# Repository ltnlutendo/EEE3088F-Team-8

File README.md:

# EEE3088F-Team-8
Team collaboration for the EEE3088F 2022, HAT project

The HAT will serve primarily as a covid compliancy monitor for enclosed public venues like
lecture theatres, classrooms and supermarkets. The Hat will be connected to a STM32
discovery board which will handle computations and other processing. It will make use of
ultrasonic sensors that will be mounted on the venue entrance to capture the number of people
entering the venue. It will also incorporate pressure and temperature sensors to specifically
monitor room ventilation and determine whether the room is safe enough for its occupants.
Besides, covid related uses, the HAT could be used to compile statistical records on lecture
attendance or supermarket peak times. Furthermore, it can be used to monitor overcrowding on
shuttles like the Jammie buses in accordance with traffic and road safety regulations.

This is an ongoing project which is constantly improved 

## What you will need:
### Hardware
```
The HAT
A 3.7 Lithium ion rechargeble battery
A USB B to USB B micro cable
A laptop (Windows/MacOS/Linux)
5V power supply
STM32 Microcontroller
```
### Software
```
Atollic Studios
```

## Setting up software

Download the Atollic Studios from [this](https://www.st.com/en/development-tools/truestudio.html#:~:text=Featured%20Videos-,Description,easy%20and%20efficient%20development%20process.)

## Connecting the HAT

### Step 1: Powering up
```
Connect the HAT to the STM32, Make sure the usb port of the micro and the microcontroller are lined up 
- if the pins are mismatched, this can lead to a short circuit
The Green LED should be on when Plug is detected
```
### Step 2: Connecting to your laptop
```
Connect the USB cable to your laptop
Then connect the micro USB B to the HAT while holding the reset button(Blue button) of the micro controller.
```
### Step 3: Programming the HAT

Open Up your Atollic Studios, fork code from this [respiratory](https://github.com/ltnlutendo/EEE3088F-Team-8)
Paste this on the terminal and Run it to the micro controller.
Set the maximum variable to Max = 3 (This will set the maximum number of people allowed to enter to 3).
The blue LED will flash twice once the code is succesfully copied to the HAT's memory.

### Step 4: Getting ready to test

```
Put the hat flat on the table such that the sensors are not obstructed (1m unobstructed minimum distance).
```
### Step 5: Test

```
Wave your hand on top of the HAT 3 times, The buzzer should beep indicating maximum number of people entered.
```
### Well Done! You're all set up.

### Project Credits
- Power Submodule  - [Lutendo Mulaisi](https://github.com/ltnlutendo) 
- Sensor Submodule   - [Munashe Chihota](https://github.com/MunasheC)
- Interfacing Submodule - [Lisakhanya Miyani](https://github.com/LisakhanyaMiyana)
## How to contribute
You can contribute to this project using these [guidelines](https://www.contributor-covenant.org/)

## License
MIT License

Copyright (c) 2022 Team 8

Permission is hereby granted, free of charge, to any person obtaining a copy
of this software and associated documentation files (the "Software"), to deal
in the Software without restriction, including without limitation the rights
to use, copy, modify, merge, publish, distribute, sublicense, and/or sell
copies of the Software, and to permit persons to whom the Software is
furnished to do so, subject to the following conditions:

The above copyright notice and this permission notice shall be included in all
copies or substantial portions of the Software.

THE SOFTWARE IS PROVIDED "AS IS", WITHOUT WARRANTY OF ANY KIND, EXPRESS OR
IMPLIED, INCLUDING BUT NOT LIMITED TO THE WARRANTIES OF MERCHANTABILITY,
FITNESS FOR A PARTICULAR PURPOSE AND NONINFRINGEMENT. IN NO EVENT SHALL THE
AUTHORS OR COPYRIGHT HOLDERS BE LIABLE FOR ANY CLAIM, DAMAGES OR OTHER
LIABILITY, WHETHER IN AN ACTION OF CONTRACT, TORT OR OTHERWISE, ARISING FROM,
OUT OF OR IN CONNECTION WITH THE SOFTWARE OR THE USE OR OTHER DEALINGS IN THE
SOFTWARE.

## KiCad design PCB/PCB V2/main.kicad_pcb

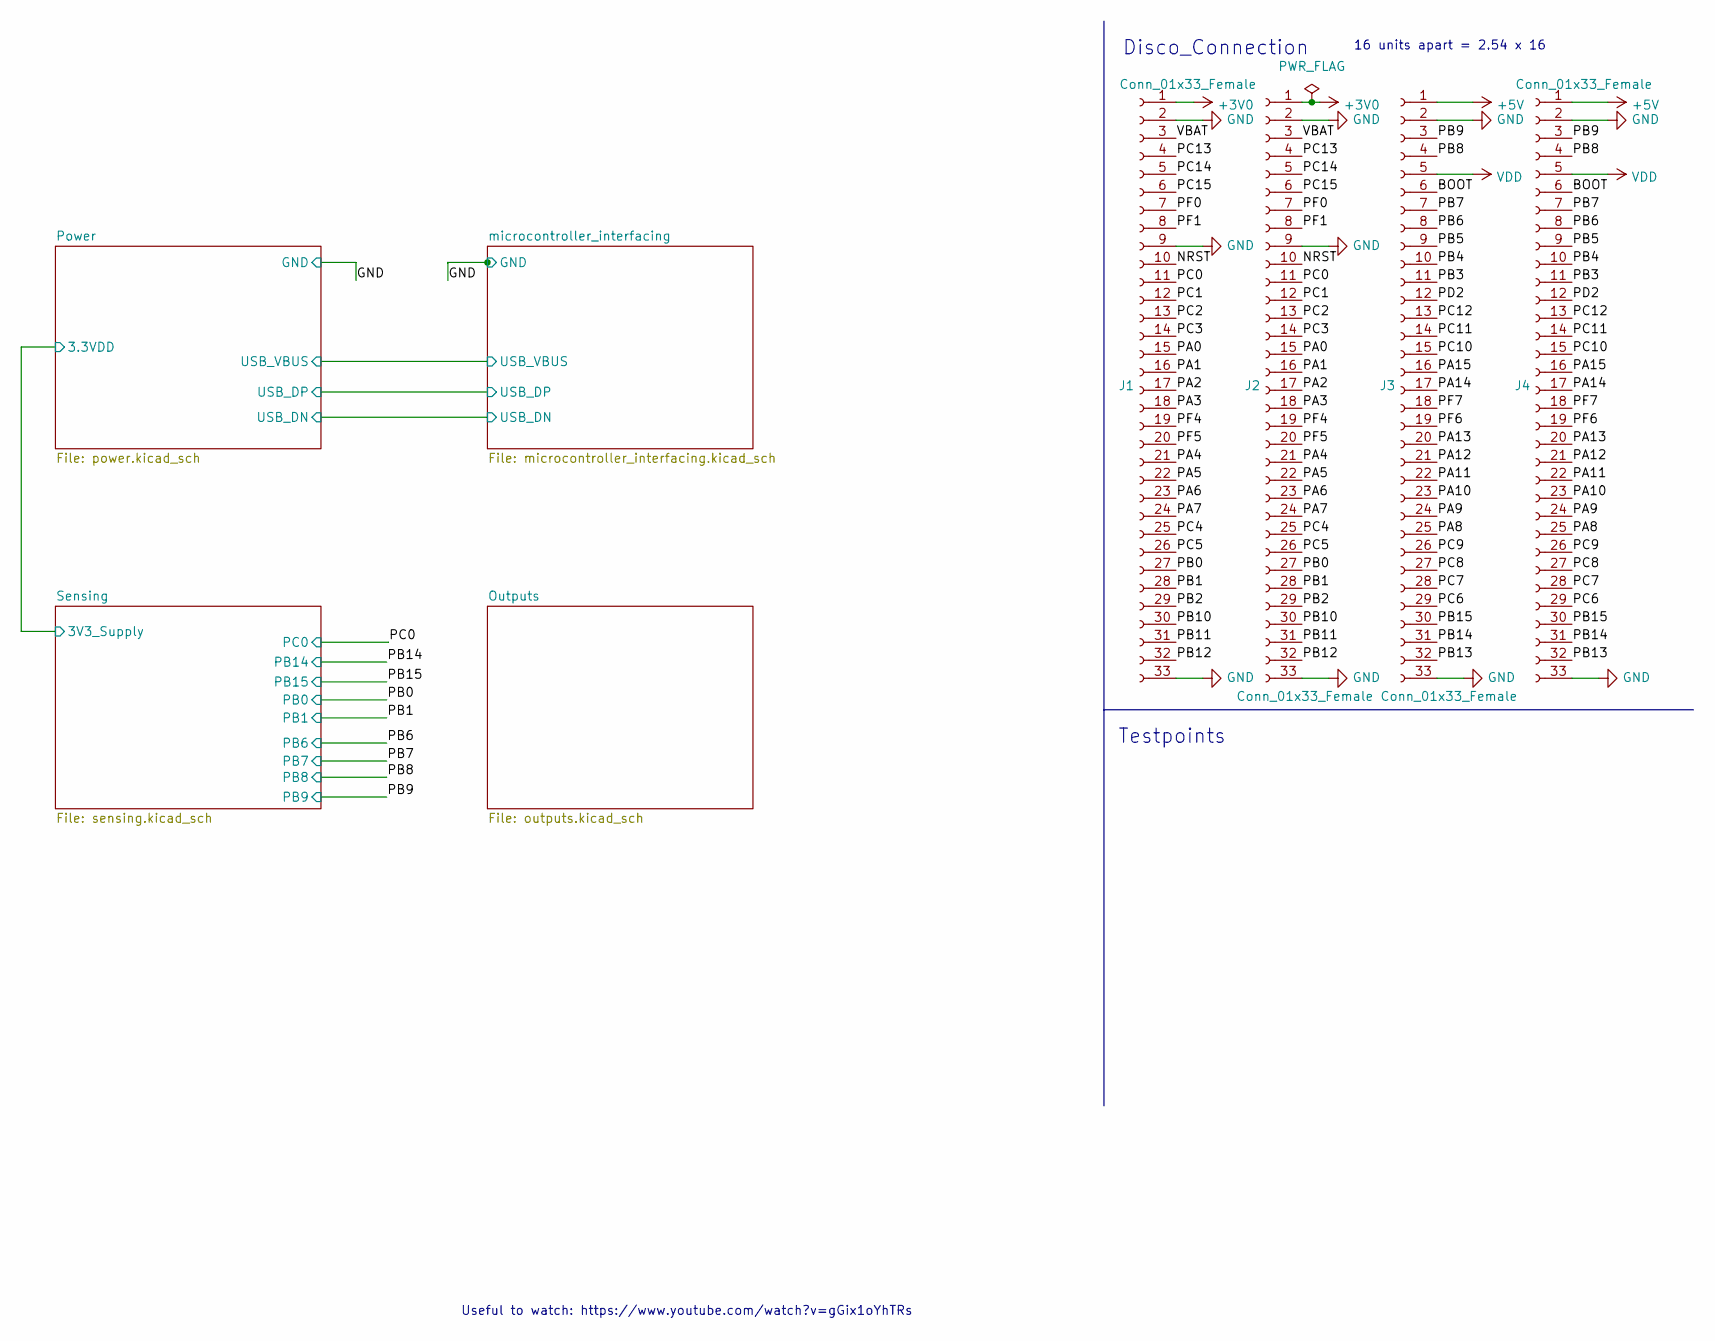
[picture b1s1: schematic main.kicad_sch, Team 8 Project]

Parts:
J1, J4: Conn_01x33_Female; PinHeader_1x33_P2.54mm_Vertical
J2, J3: Conn_01x33_Female; PinSocket_1x33_P2.54mm_Vertical; LCSC C1234 (example)

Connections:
+3V0: J1.1, J2.1
+3V3: J3.5, J4.5; also elsewhere on the board
/BOOT: J3.6, J4.6
/NRST: J1.10, J2.10
/PA0: J1.15, J2.15
/PA1: J1.16, J2.16
/PA2: J1.17, J2.17
/PA3: J1.18, J2.18
/PA4: J1.21, J2.21
/PA5: J1.22, J2.22
/PA6: J1.23, J2.23
/PA7: J1.24, J2.24
/PA8: J3.25, J4.25
/PA9: J3.24, J4.24
/PA10: J3.23, J4.23
/PA11: J3.22, J4.22
/PA12: J3.21, J4.21
/PA13: J3.20, J4.20
/PA14: J3.17, J4.17
/PA15: J3.16, J4.16
/PB0: J1.27, J2.27; also elsewhere on the board
/PB1: J1.28, J2.28; also elsewhere on the board
/PB2: J1.29, J2.29
/PB3: J3.11, J4.11
/PB4: J3.10, J4.10
/PB5: J3.9, J4.9
/PB6: J3.8, J4.8; also elsewhere on the board
/PB7: J3.7, J4.7; also elsewhere on the board
/PB8: J3.4, J4.4; also elsewhere on the board
/PB9: J3.3, J4.3; also elsewhere on the board
/PB10: J1.30, J2.30
/PB11: J1.31, J2.31
/PB12: J1.32, J2.32
/PB13: J3.32, J4.32
/PB14: J3.31, J4.31; also elsewhere on the board
/PB15: J3.30, J4.30; also elsewhere on the board
/PC0: J1.11, J2.11; also elsewhere on the board
/PC1: J1.12, J2.12
/PC2: J1.13, J2.13
/PC3: J1.14, J2.14
/PC4: J1.25, J2.25
/PC5: J1.26, J2.26
/PC6: J3.29, J4.29
/PC7: J3.28, J4.28
/PC8: J3.27, J4.27
/PC9: J3.26, J4.26
/PC10: J3.15, J4.15
/PC11: J3.14, J4.14
/PC12: J3.13, J4.13
/PC13: J1.4, J2.4
/PC14: J1.5, J2.5
/PC15: J1.6, J2.6
/PD2: J3.12, J4.12
/PF0: J1.7, J2.7
/PF1: J1.8, J2.8
/PF4: J1.19, J2.19
/PF5: J1.20, J2.20
/PF6: J3.19, J4.19
/PF7: J3.18, J4.18
/VBAT: J1.3, J2.3
GND: J1.2, J1.9, J1.33, J2.2, J2.9, J2.33, J3.2, J3.33, J4.2, J4.33; also elsewhere on the board

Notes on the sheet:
Useful to watch: https://www.youtube.com/watch?v=gGix1oYhTRs
16 units apart = 2.54 x 16
Disco_Connection
Testpoints

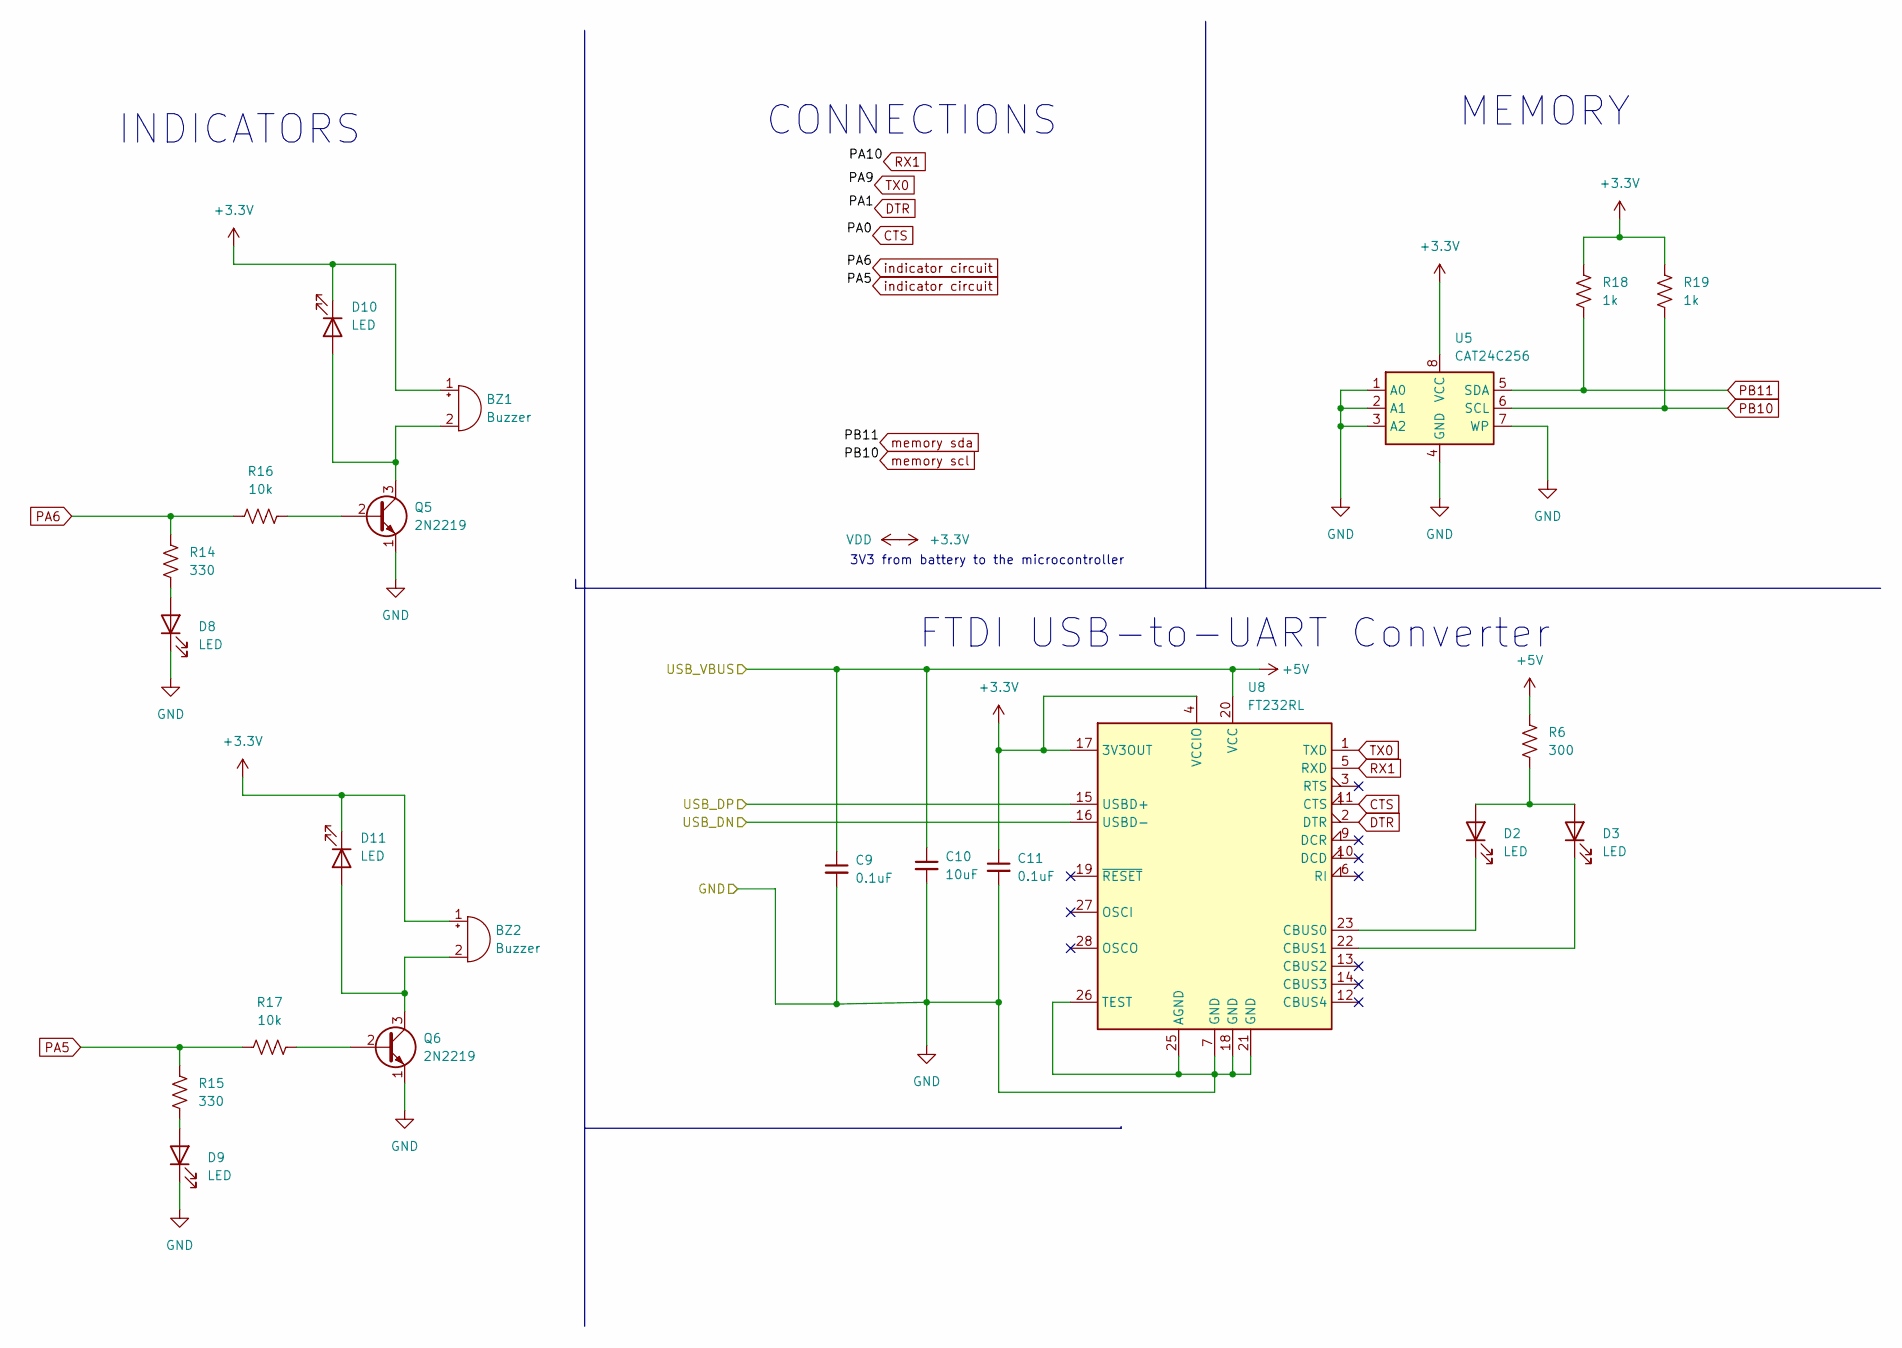
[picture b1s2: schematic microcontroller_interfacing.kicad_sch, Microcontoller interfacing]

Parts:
BZ1, BZ2: Buzzer; Buzzer_Murata_PKLCS1212E
C9, C11: 0.1uF; C_0805_2012Metric_Pad1.18x1.45mm_HandSolder
C10: 10uF; C_0805_2012Metric_Pad1.18x1.45mm_HandSolder
D2, D3, D8, D9, D10, D11: LED; LED_0805_2012Metric_Pad1.15x1.40mm_HandSolder
Q5, Q6: 2N2219; TO-39-3
R6: 300; R_0805_2012Metric_Pad1.20x1.40mm_HandSolder
R14, R15: 330; R_0805_2012Metric_Pad1.20x1.40mm_HandSolder
R16, R17: 10k; R_0805_2012Metric_Pad1.20x1.40mm_HandSolder
R18: 1k; R_0805_2012Metric_Pad1.20x1.40mm_HandSolder
R19: 1k; R_0805_2012Metric
U5: CAT24C256; SOIC-8_3.9x4.9mm_P1.27mm
U8: FT232RL; SSOP-28_5.3x10.2mm_P0.65mm

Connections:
+3V3: BZ1.1 (-), BZ2.1 (-), C11.1, D10.1 (K), D11.1 (K), R18.2, R19.2, U5.8 (VCC), U8.4 (VCCIO), U8.17 (3V3OUT); also elsewhere on the board
/Power/USB_DN: U8.16 (USBD-); also elsewhere on the board
/Power/USB_DP: U8.15 (USBD+); also elsewhere on the board
CTS: U8.11 (CTS)
DTR: U8.2 (DTR)
GND: C9.2, C10.2, C11.2, D8.1 (K), D9.1 (K), Q5.1 (E), Q6.1 (E), U5.1 (A0), U5.2 (A1), U5.3 (A2), U5.4 (GND), U5.7 (WP), U8.7 (GND), U8.18 (GND), U8.21 (GND), U8.25 (AGND), U8.26 (TEST); also elsewhere on the board
unnamed: BZ1.2 (+), D10.2 (A), Q5.3 (C)
unnamed: BZ2.2 (+), D11.2 (A), Q6.3 (C)
unnamed: D2.1 (K), U8.23 (CBUS0)
unnamed: D2.2 (A), D3.2 (A), R6.2
unnamed: D3.1 (K), U8.22 (CBUS1)
unnamed: D8.2 (A), R14.1
unnamed: D9.2 (A), R15.1
unnamed: Q5.2 (B), R16.2
unnamed: Q6.2 (B), R17.2
PB10: R19.1, U5.6 (SCL)
PB11: R18.1, U5.5 (SDA)
RX1: U8.5 (RXD)
TX0: U8.1 (TXD)

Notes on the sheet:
CONNECTIONS
MEMORY
FTDI USB-to-UART Converter
3V3 from battery to the microcontroller
INDICATORS

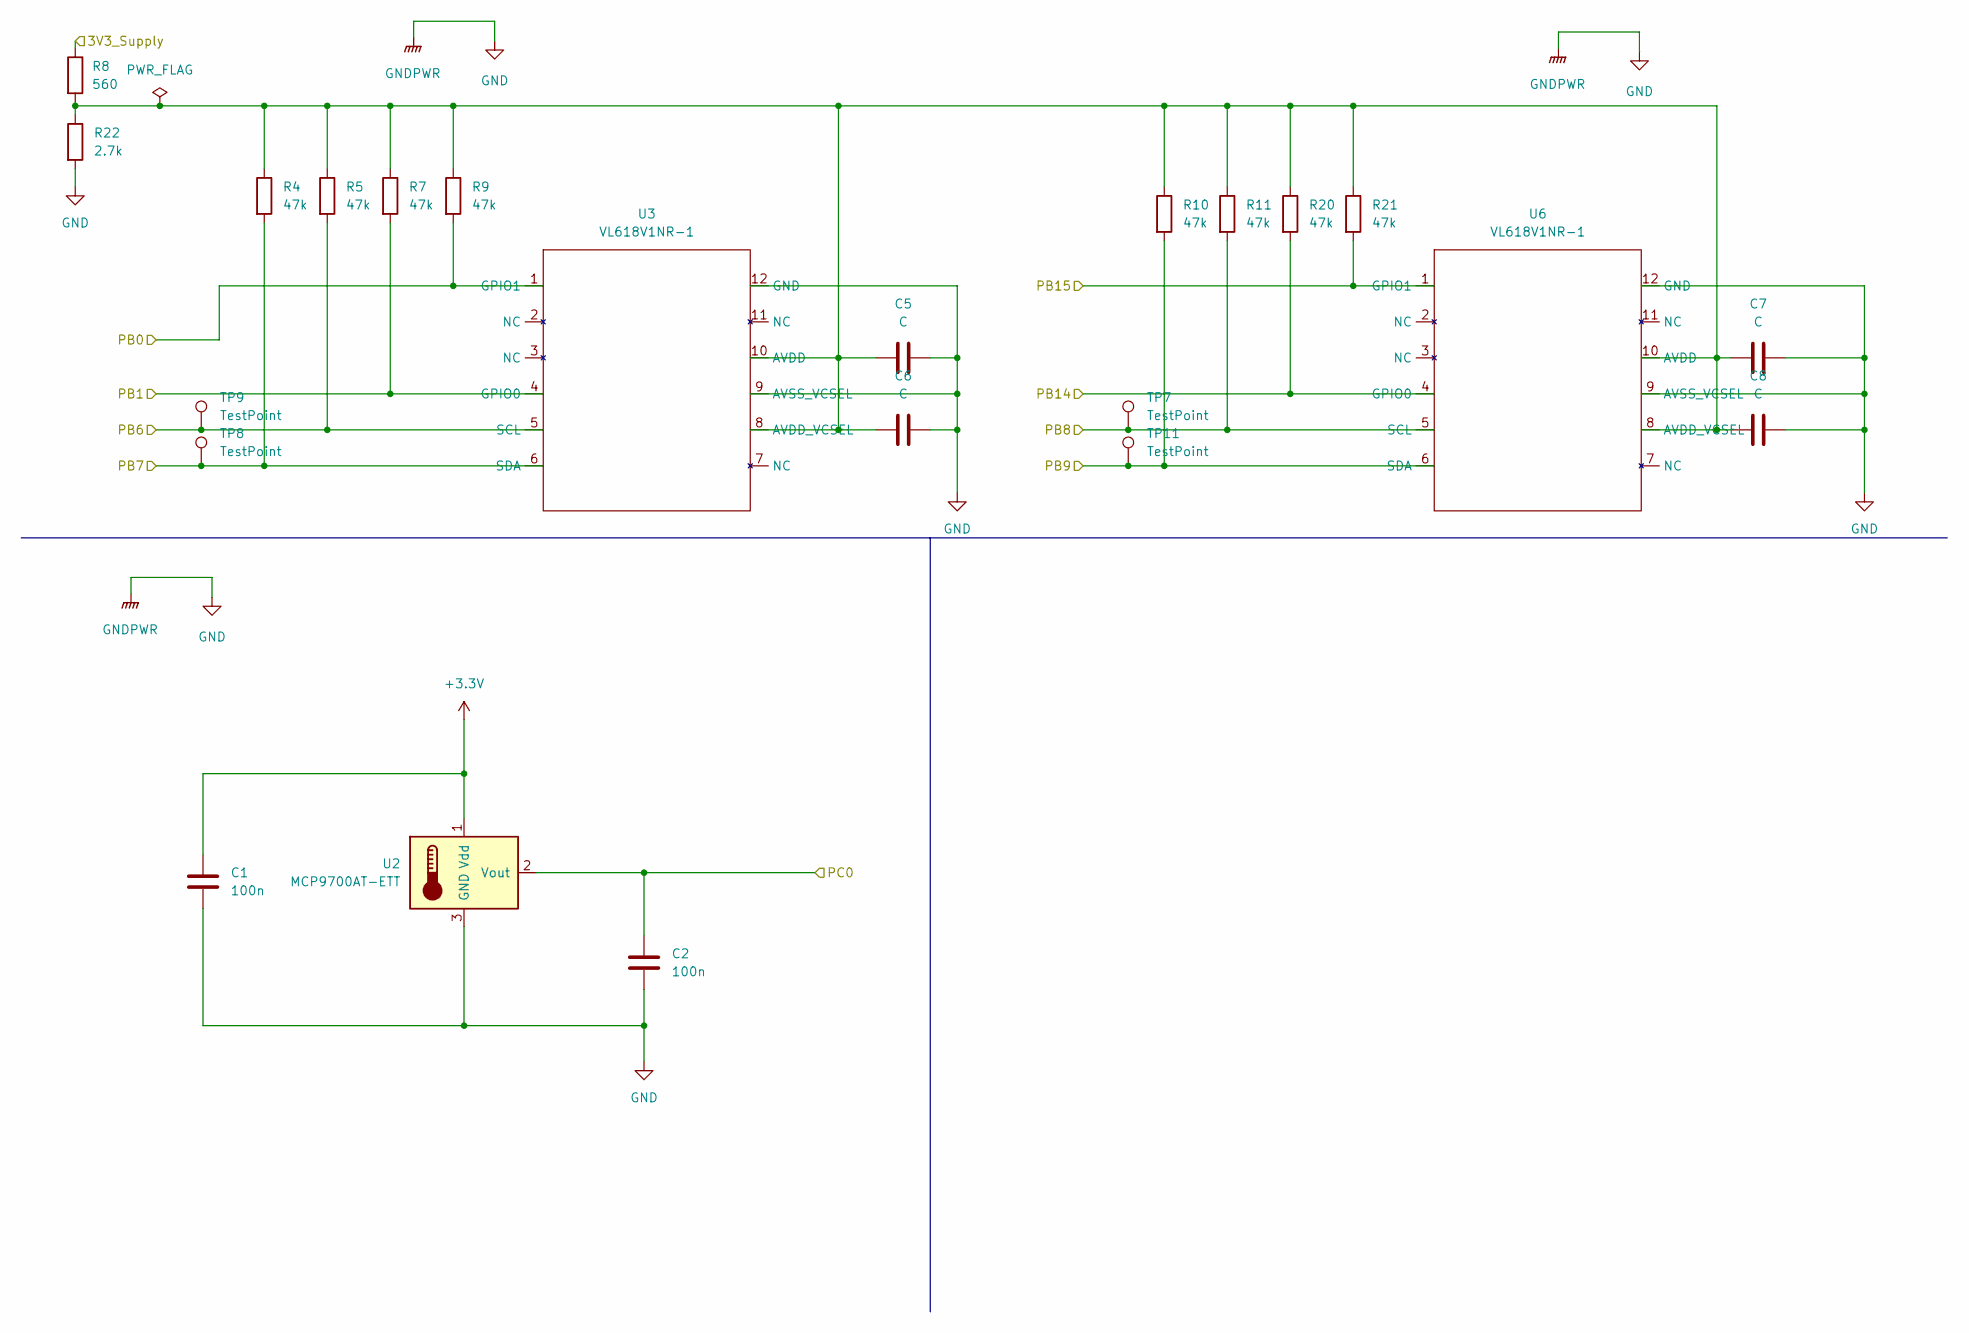
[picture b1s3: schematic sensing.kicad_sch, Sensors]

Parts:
C1, C2: 100n; C_0805_2012Metric_Pad1.18x1.45mm_HandSolder
C5, C6, C7, C8: C; C_0805_2012Metric_Pad1.18x1.45mm_HandSolder
R4, R5, R7, R9, R10, R11, R20, R21: 47k; R_0805_2012Metric_Pad1.20x1.40mm_HandSolder
R8: 560; R_0805_2012Metric_Pad1.20x1.40mm_HandSolder
R22: 2.7k; R_0805_2012Metric_Pad1.20x1.40mm_HandSolder
TP7, TP8, TP9, TP11: TestPoint; PinHeader_1x01_P2.54mm_Vertical
U2: MCP9700AT-ETT; SOT-23
U3, U6: VL618V1NR-1; VL6180

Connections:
+3V3: C1.1, U2.1 (Vdd); also elsewhere on the board
/PB0: R9.2, U3.1 (GPIO1); also elsewhere on the board
/PB1: R7.2, U3.4 (GPIO0); also elsewhere on the board
/PB6: R5.2, TP9.1, U3.5 (SCL); also elsewhere on the board
/PB7: R4.2, TP8.1, U3.6 (SDA); also elsewhere on the board
/PB8: R11.2, TP7.1, U6.5 (SCL); also elsewhere on the board
/PB9: R10.2, TP11.1, U6.6 (SDA); also elsewhere on the board
/PB14: R20.2, U6.4 (GPIO0); also elsewhere on the board
/PB15: R21.2, U6.1 (GPIO1); also elsewhere on the board
/PC0: C2.1, U2.2 (Vout); also elsewhere on the board
/Power/3.3VDD: R8.1; also elsewhere on the board
GND: C1.2, C2.2, C5.2, C6.2, C7.1, C8.2, R22.2, U2.3 (GND), U3.9 (AVSS_VCSEL), U3.12 (GND), U6.9 (AVSS_VCSEL), U6.12 (GND); also elsewhere on the board
unnamed: C5.1, C6.1, C7.2, C8.1, R4.1, R5.1, R7.1, R8.2, R9.1, R10.1, R11.1, R20.1, R21.1, R22.1, U3.8 (AVDD_VCSEL), U3.10 (AVDD), U6.8 (AVDD_VCSEL), U6.10 (AVDD)

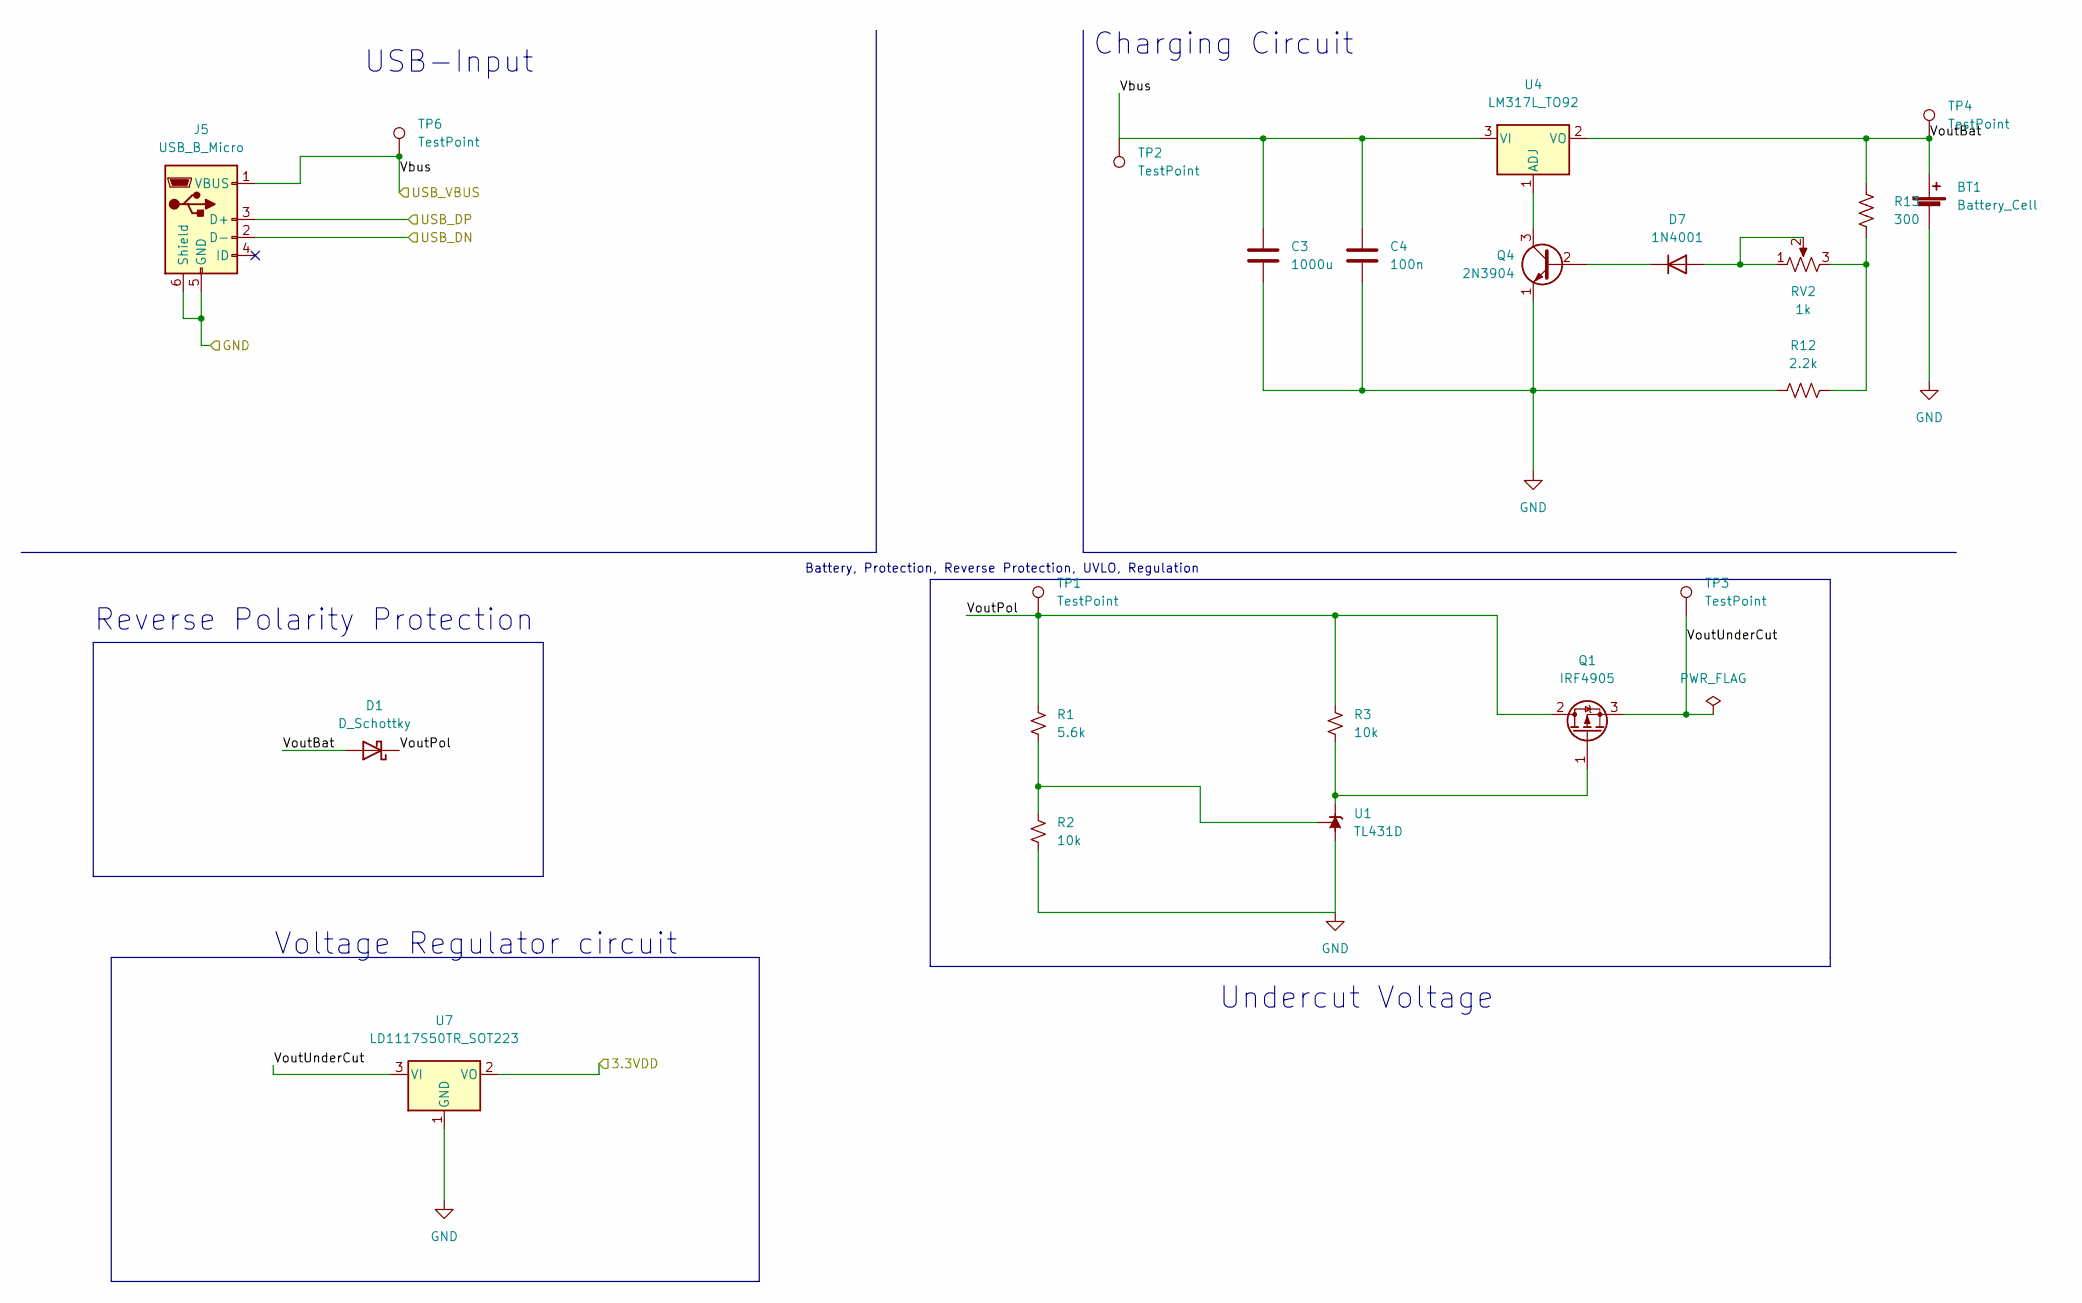
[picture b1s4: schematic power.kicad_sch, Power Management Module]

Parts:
BT1: Battery_Cell; BatteryHolder_Keystone_1042_1x18650
C3: 1000u; C_0805_2012Metric_Pad1.18x1.45mm_HandSolder
C4: 100n; C_0805_2012Metric_Pad1.18x1.45mm_HandSolder
D1: D_Schottky; D_SOD-123
D7: 1N4001; D_DO-41_SOD81_P10.16mm_Horizontal
J5: USB_B_Micro; USB_Micro-B_Amphenol_10103594-0001LF_Horizontal
Q1: IRF4905; TO-220-3_Vertical
Q4: 2N3904; TO-39-3
R1: 5.6k; R_0805_2012Metric_Pad1.20x1.40mm_HandSolder
R2, R3: 10k; R_0805_2012Metric_Pad1.20x1.40mm_HandSolder
R12: 2.2k; R_0805_2012Metric_Pad1.20x1.40mm_HandSolder
R13: 300; R_0805_2012Metric_Pad1.20x1.40mm_HandSolder
RV2: 1k; Potentiometer_Bourns_3224J_Horizontal
TP1, TP2, TP3, TP4, TP6: TestPoint; PinHeader_1x01_P2.54mm_Vertical
U1: TL431D; SOIC-8_3.9x4.9mm_P1.27mm
U4: LM317L_TO92; TO-92_Inline
U7: LD1117S50TR_SOT223; SOT-223-3_TabPin2

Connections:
/Power/3.3VDD: U7.2 (VO); also elsewhere on the board
/Power/USB_DN: J5.2 (D-); also elsewhere on the board
/Power/USB_DP: J5.3 (D+); also elsewhere on the board
/Power/VoutPol: D1.1 (K), Q1.2 (D), R1.1, R3.1, TP1.1
/Power/VoutUnderCut: Q1.3 (S), TP3.1, U7.3 (VI)
GND: BT1.2 (-), C3.2, C4.2, J5.5 (GND), J5.6 (Shield), Q4.1 (E), R2.2, R12.1, U1.2 (A), U1.3 (A), U1.6 (A), U1.7 (A), U7.1 (GND); also elsewhere on the board
unnamed: D7.1 (K), Q4.2 (B)
unnamed: D7.2 (A), RV2.1, RV2.2
unnamed: Q1.1 (G), R3.2, U1.1 (K)
unnamed: Q4.3 (C), U4.1 (ADJ)
unnamed: R1.2, R2.1, U1.8 (REF)
unnamed: R12.2, R13.2, RV2.3

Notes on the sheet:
Reverse Polarity Protection
USB-Input
Undercut Voltage
Voltage Regulator circuit
Charging Circuit
Battery, Protection, Reverse Protection, UVLO, Regulation

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
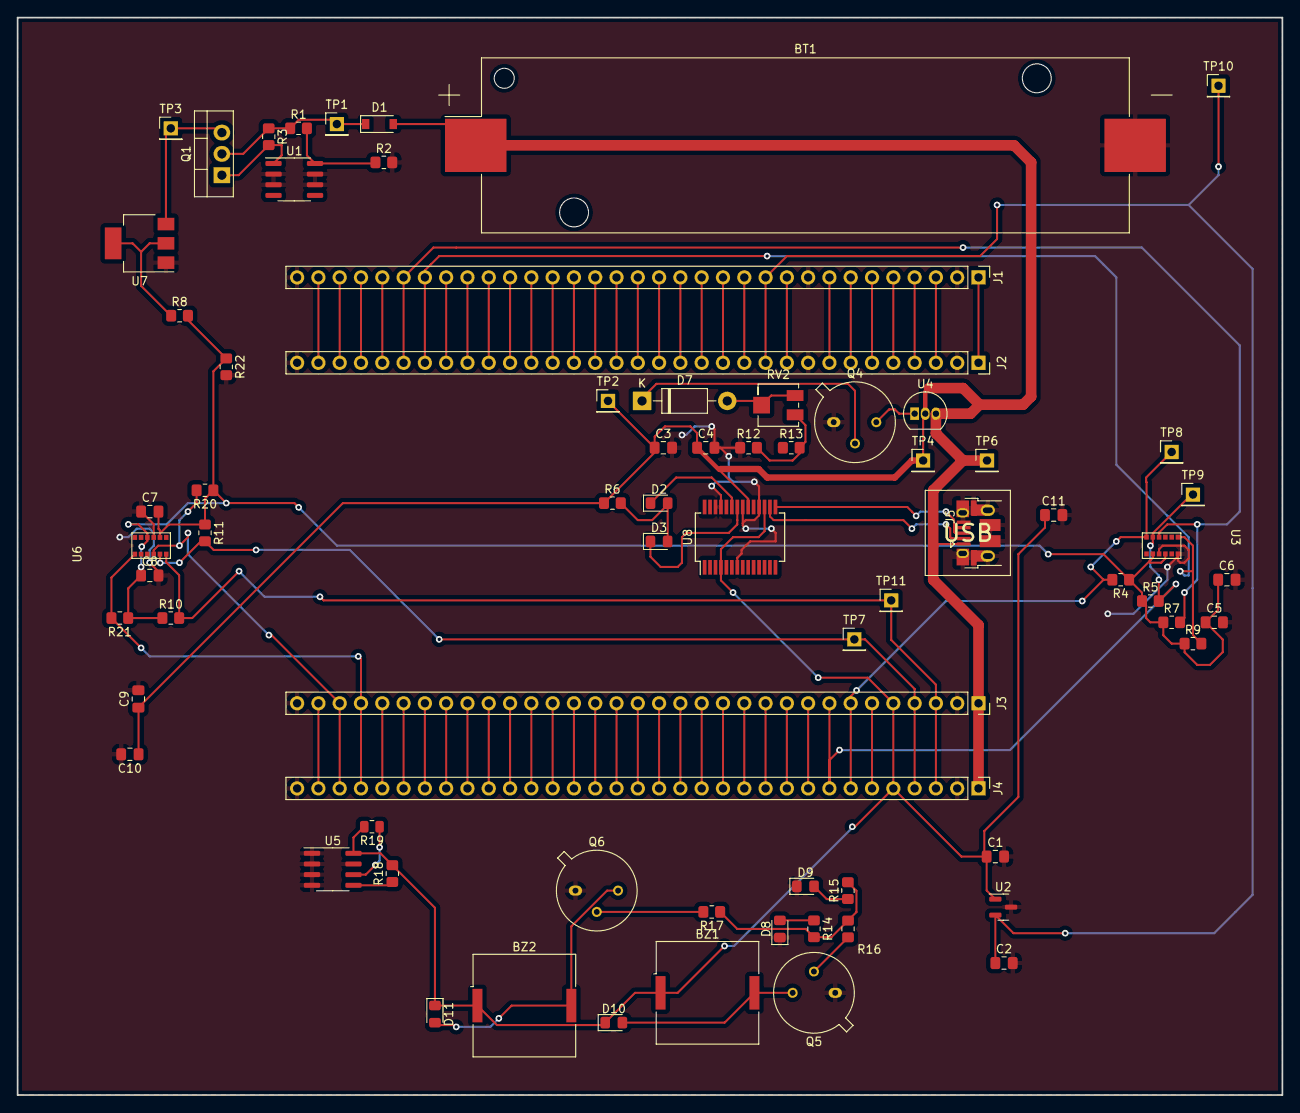
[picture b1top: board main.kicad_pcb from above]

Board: 2 copper layers, 150.9 x 128.5 mm, 72 parts (0 on the bottom side), 86 nets.

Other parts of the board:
TP10: TestPoint; PinHeader_1x01_P2.54mm_Vertical

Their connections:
/PC0: TP10.1; also elsewhere on the board

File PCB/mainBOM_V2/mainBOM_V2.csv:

Reference(s);Component Name and Value;LibPart;Footprint and part number;Component Price ($)
BT1;Battery_Cell;Device:Battery_Cell;Battery:BatteryHolder_Keystone_1042_1x18650;4
BZ1;Buzzer;Device:Buzzer;Buzzer_Beeper:Buzzer_Murata_PKLCS1212E;0,267
BZ2;Buzzer;Device:Buzzer;Buzzer_Beeper:Buzzer_Murata_PKLCS1212E;0,267
C1;100n;Device:C;Capacitor_SMD:C_0805_2012Metric_Pad1.18x1.45mm_HandSolder;0,18
C2;100n;Device:C;Capacitor_SMD:C_0805_2012Metric_Pad1.18x1.45mm_HandSolder;0,18
C3;1000u;Device:C;Capacitor_SMD:C_0805_2012Metric_Pad1.18x1.45mm_HandSolder;0,18
C4;100n;Device:C;Capacitor_SMD:C_0805_2012Metric_Pad1.18x1.45mm_HandSolder;0,18
C5;C;Device:C;Capacitor_SMD:C_0805_2012Metric_Pad1.18x1.45mm_HandSolder;0,18
C6;C;Device:C;Capacitor_SMD:C_0805_2012Metric_Pad1.18x1.45mm_HandSolder;0,18
C7;C;Device:C;Capacitor_SMD:C_0805_2012Metric_Pad1.18x1.45mm_HandSolder;0,18
C8;C;Device:C;Capacitor_SMD:C_0805_2012Metric_Pad1.18x1.45mm_HandSolder;0,18
C9;0.1uF;Device:C_Small;Capacitor_SMD:C_0805_2012Metric_Pad1.18x1.45mm_HandSolder;0,18
C10;10uF;Device:C_Small;Capacitor_SMD:C_0805_2012Metric_Pad1.18x1.45mm_HandSolder;0,18
C11;0.1uF;Device:C_Small;Capacitor_SMD:C_0805_2012Metric_Pad1.18x1.45mm_HandSolder;0,18
D1;D_Schottky;Device:D_Schottky;Diode_SMD:D_SOD-123;0,37
D2;LED;Device:LED;LED_SMD:LED_0805_2012Metric_Pad1.15x1.40mm_HandSolder;0,015
D3;LED;Device:LED;LED_SMD:LED_0805_2012Metric_Pad1.15x1.40mm_HandSolder;0,015
D7;1N4001;Diode:1N4001;Diode_THT:D_DO-41_SOD81_P10.16mm_Horizontal;0,1
D8;LED;Device:LED;LED_SMD:LED_0805_2012Metric_Pad1.15x1.40mm_HandSolder;0,015
D9;LED;Device:LED;LED_SMD:LED_0805_2012Metric_Pad1.15x1.40mm_HandSolder;0,015
D10;LED;Device:LED;LED_SMD:LED_0805_2012Metric_Pad1.15x1.40mm_HandSolder;0,015
D11;LED;Device:LED;LED_SMD:LED_0805_2012Metric_Pad1.15x1.40mm_HandSolder;0,015
J1;Conn_01x33_Female;Connector:Conn_01x33_Female;Connector_PinHeader_2.54mm:PinHeader_1x33_P2.54mm_Vertical;0
J2;Conn_01x33_Female;Connector:Conn_01x33_Female;Connector_PinSocket_2.54mm:PinSocket_1x33_P2.54mm_Vertical;0
J3;Conn_01x33_Female;Connector:Conn_01x33_Female;Connector_PinSocket_2.54mm:PinSocket_1x33_P2.54mm_Vertical;0
J4;Conn_01x33_Female;Connector:Conn_01x33_Female;Connector_PinHeader_2.54mm:PinHeader_1x33_P2.54mm_Vertical;0
J5;USB_B_Micro;Connector:USB_B_Micro;Connector_USB:USB_Micro-B_Amphenol_10103594-0001LF_Horizontal;3,075
Q1;IRF4905;Transistor_FET:IRF4905;Package_TO_SOT_THT:TO-220-3_Vertical;0,25
Q4;2N3904;Transistor_BJT:2N3904;Package_TO_SOT_THT:TO-39-3;0,2
Q5;2N2219;Transistor_BJT:2N2219;Package_TO_SOT_THT:TO-39-3;0,2
Q6;2N2219;Transistor_BJT:2N2219;Package_TO_SOT_THT:TO-39-3;0,2
R1;5.6k;Device:R_Small_US;Resistor_SMD:R_0805_2012Metric_Pad1.20x1.40mm_HandSolder;0,007
R2;10k;Device:R_Small_US;Resistor_SMD:R_0805_2012Metric_Pad1.20x1.40mm_HandSolder;0,007
R3;10k;Device:R_Small_US;Resistor_SMD:R_0805_2012Metric_Pad1.20x1.40mm_HandSolder;0,007
R4;47k;Device:R;Resistor_SMD:R_0805_2012Metric_Pad1.20x1.40mm_HandSolder;0,007
R5;47k;Device:R;Resistor_SMD:R_0805_2012Metric_Pad1.20x1.40mm_HandSolder;0,007
R6;300;Device:R_US;Resistor_SMD:R_0805_2012Metric_Pad1.20x1.40mm_HandSolder;0,007
R7;47k;Device:R;Resistor_SMD:R_0805_2012Metric_Pad1.20x1.40mm_HandSolder;0,007
R8;560;Device:R;Resistor_SMD:R_0805_2012Metric_Pad1.20x1.40mm_HandSolder;0,007
R9;47k;Device:R;Resistor_SMD:R_0805_2012Metric_Pad1.20x1.40mm_HandSolder;0,007
R10;47k;Device:R;Resistor_SMD:R_0805_2012Metric_Pad1.20x1.40mm_HandSolder;0,007
R11;47k;Device:R;Resistor_SMD:R_0805_2012Metric_Pad1.20x1.40mm_HandSolder;0,007
R12;2.2k;Device:R_US;Resistor_SMD:R_0805_2012Metric_Pad1.20x1.40mm_HandSolder;0,007
R13;300;Device:R_US;Resistor_SMD:R_0805_2012Metric_Pad1.20x1.40mm_HandSolder;0,007
R14;330;Device:R_US;Resistor_SMD:R_0805_2012Metric_Pad1.20x1.40mm_HandSolder;0,007
R15;330;Device:R_US;Resistor_SMD:R_0805_2012Metric_Pad1.20x1.40mm_HandSolder;0,007
R16;10k;Device:R_US;Resistor_SMD:R_0805_2012Metric_Pad1.20x1.40mm_HandSolder;0,007
R17;10k;Device:R_US;Resistor_SMD:R_0805_2012Metric_Pad1.20x1.40mm_HandSolder;0,007
R18;1k;Device:R_US;Resistor_SMD:R_0805_2012Metric_Pad1.20x1.40mm_HandSolder;0,007
R19;1k;Device:R_US;Resistor_SMD:R_0805_2012Metric;0,007
R20;47k;Device:R;Resistor_SMD:R_0805_2012Metric_Pad1.20x1.40mm_HandSolder;0,007
R21;47k;Device:R;Resistor_SMD:R_0805_2012Metric_Pad1.20x1.40mm_HandSolder;0,007
R22;2.7k;Device:R;Resistor_SMD:R_0805_2012Metric_Pad1.20x1.40mm_HandSolder;0,007
RV2;1k;Device:R_Potentiometer_US;Potentiometer_SMD:Potentiometer_Bourns_3224J_Horizontal;3,1698
TP1;TestPoint;Connector:TestPoint;Connector_PinHeader_2.54mm:PinHeader_1x01_P2.54mm_Vertical;0,01
TP2;TestPoint;Connector:TestPoint;Connector_PinHeader_2.54mm:PinHeader_1x01_P2.54mm_Vertical;0,01
TP3;TestPoint;Connector:TestPoint;Connector_PinHeader_2.54mm:PinHeader_1x01_P2.54mm_Vertical;0,01
TP4;TestPoint;Connector:TestPoint;Connector_PinHeader_2.54mm:PinHeader_1x01_P2.54mm_Vertical;0,01
TP6;TestPoint;Connector:TestPoint;Connector_PinHeader_2.54mm:PinHeader_1x01_P2.54mm_Vertical;0,01
TP7;TestPoint;Connector:TestPoint;Connector_PinHeader_2.54mm:PinHeader_1x01_P2.54mm_Vertical;0,01
TP8;TestPoint;Connector:TestPoint;Connector_PinHeader_2.54mm:PinHeader_1x01_P2.54mm_Vertical;0,01
TP9;TestPoint;Connector:TestPoint;Connector_PinHeader_2.54mm:PinHeader_1x01_P2.54mm_Vertical;0,01
TP11;TestPoint;Connector:TestPoint;Connector_PinHeader_2.54mm:PinHeader_1x01_P2.54mm_Vertical;0,01
U1;TL431D;Reference_Voltage:TL431D;Package_SO:SOIC-8_3.9x4.9mm_P1.27mm;0,02
U2;MCP9700AT-ETT;Sensor_Temperature:MCP9700AT-ETT;Package_TO_SOT_SMD:SOT-23;0,863
U3;VL618V1NR-1;:VL618V1NR-1_1;ProjectLibFootprints:VL6180;1,9541
U4;LM317L_TO92;Regulator_Linear:LM317L_TO92;Package_TO_SOT_THT:TO-92_Inline;0,2384
U5;CAT24C256;Memory_EEPROM:CAT24C256;Package_SO:SOIC-8_3.9x4.9mm_P1.27mm;3,5
U6;VL618V1NR-1;Project sensors:VL618V1NR-1;ProjectLibFootprints:VL6180;1,9541
U7;LD1117S50TR_SOT223;Regulator_Linear:LD1117S50TR_SOT223;Package_TO_SOT_SMD:SOT-223-3_TabPin2;0,1856
U8;FT232RL;Interface_USB:FT232RL;Package_SO:SSOP-28_5.3x10.2mm_P0.65mm;3,7938

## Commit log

2022-02-24 Create Gerbers
2022-03-18 Create mainv02
2022-03-20 Create mainv03\
2022-03-20 Create completeSchematic1
2022-03-20 Create main
2022-04-22 Update LICENSE
2022-04-24 Create rea
2022-04-24 Rename rea to read.md
2022-04-24 Create BOM
